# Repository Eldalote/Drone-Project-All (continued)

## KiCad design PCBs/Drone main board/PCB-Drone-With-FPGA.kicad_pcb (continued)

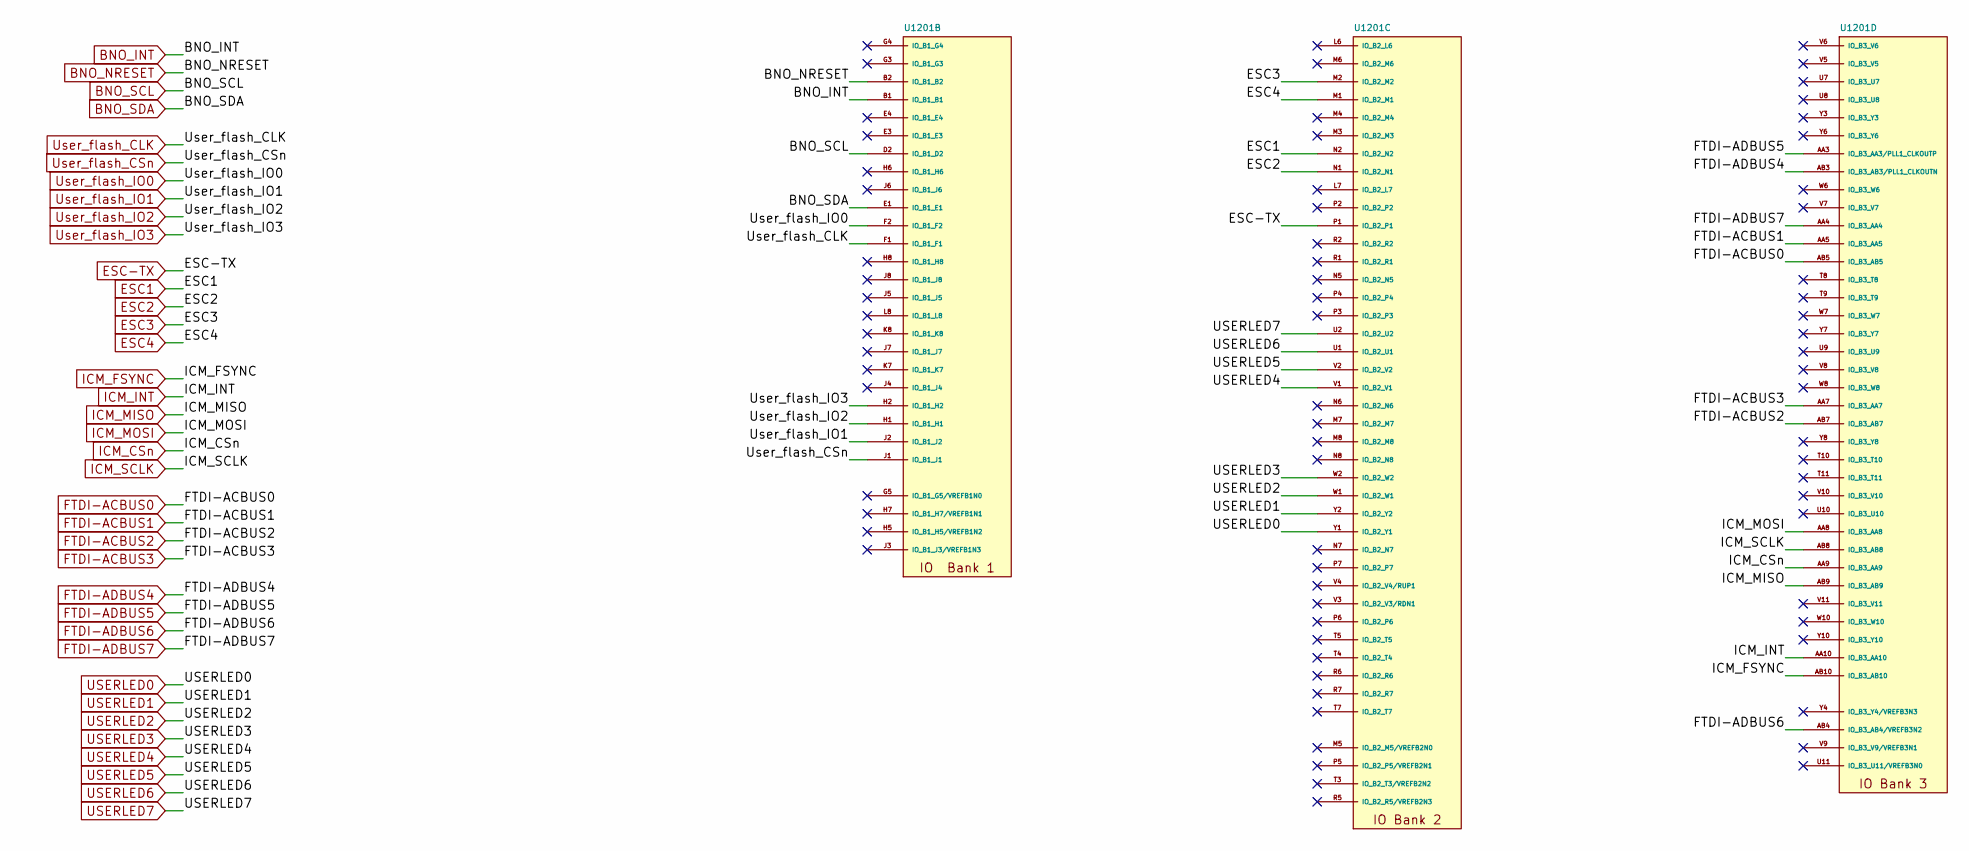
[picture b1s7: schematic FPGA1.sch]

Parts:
U1201: 10CL040_F484; BGA484C100P22X22_2300X2300X200

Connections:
BNO_INT: U1201.B1 (IO_B1_B1); also elsewhere on the board
BNO_NRESET: U1201.B2 (IO_B1_B2); also elsewhere on the board
BNO_SCL: U1201.D2 (IO_B1_D2); also elsewhere on the board
BNO_SDA: U1201.E1 (IO_B1_E1); also elsewhere on the board
ESC1: U1201.N2 (IO_B2_N2); also elsewhere on the board
ESC2: U1201.N1 (IO_B2_N1); also elsewhere on the board
ESC3: U1201.M2 (IO_B2_M2); also elsewhere on the board
ESC4: U1201.M1 (IO_B2_M1); also elsewhere on the board
ESC-TX: U1201.P1 (IO_B2_P1); also elsewhere on the board
FTDI-ACBUS0: U1201.AB5 (IO_B3_AB5); also elsewhere on the board
FTDI-ACBUS1: U1201.AA5 (IO_B3_AA5); also elsewhere on the board
FTDI-ACBUS2: U1201.AB7 (IO_B3_AB7); also elsewhere on the board
FTDI-ACBUS3: U1201.AA7 (IO_B3_AA7); also elsewhere on the board
FTDI-ADBUS4: U1201.AB3 (IO_B3_AB3/PLL1_CLKOUTN); also elsewhere on the board
FTDI-ADBUS5: U1201.AA3 (IO_B3_AA3/PLL1_CLKOUTP); also elsewhere on the board
FTDI-ADBUS6: U1201.AB4 (IO_B3_AB4/VREFB3N2); also elsewhere on the board
FTDI-ADBUS7: U1201.AA4 (IO_B3_AA4); also elsewhere on the board
ICM_CSn: U1201.AA9 (IO_B3_AA9); also elsewhere on the board
ICM_FSYNC: U1201.AB10 (IO_B3_AB10); also elsewhere on the board
ICM_INT: U1201.AA10 (IO_B3_AA10); also elsewhere on the board
ICM_MISO: U1201.AB9 (IO_B3_AB9); also elsewhere on the board
ICM_MOSI: U1201.AA8 (IO_B3_AA8); also elsewhere on the board
ICM_SCLK: U1201.AB8 (IO_B3_AB8); also elsewhere on the board
USERLED0: U1201.Y1 (IO_B2_Y1); also elsewhere on the board
USERLED1: U1201.Y2 (IO_B2_Y2); also elsewhere on the board
USERLED2: U1201.W1 (IO_B2_W1); also elsewhere on the board
USERLED3: U1201.W2 (IO_B2_W2); also elsewhere on the board
USERLED4: U1201.V1 (IO_B2_V1); also elsewhere on the board
USERLED5: U1201.V2 (IO_B2_V2); also elsewhere on the board
USERLED6: U1201.U1 (IO_B2_U1); also elsewhere on the board
USERLED7: U1201.U2 (IO_B2_U2); also elsewhere on the board
User_flash_CLK: U1201.F1 (IO_B1_F1); also elsewhere on the board
User_flash_CSn: U1201.J1 (IO_B1_J1); also elsewhere on the board
User_flash_IO0: U1201.F2 (IO_B1_F2); also elsewhere on the board
User_flash_IO1: U1201.J2 (IO_B1_J2); also elsewhere on the board
User_flash_IO2: U1201.H1 (IO_B1_H1); also elsewhere on the board
User_flash_IO3: U1201.H2 (IO_B1_H2); also elsewhere on the board

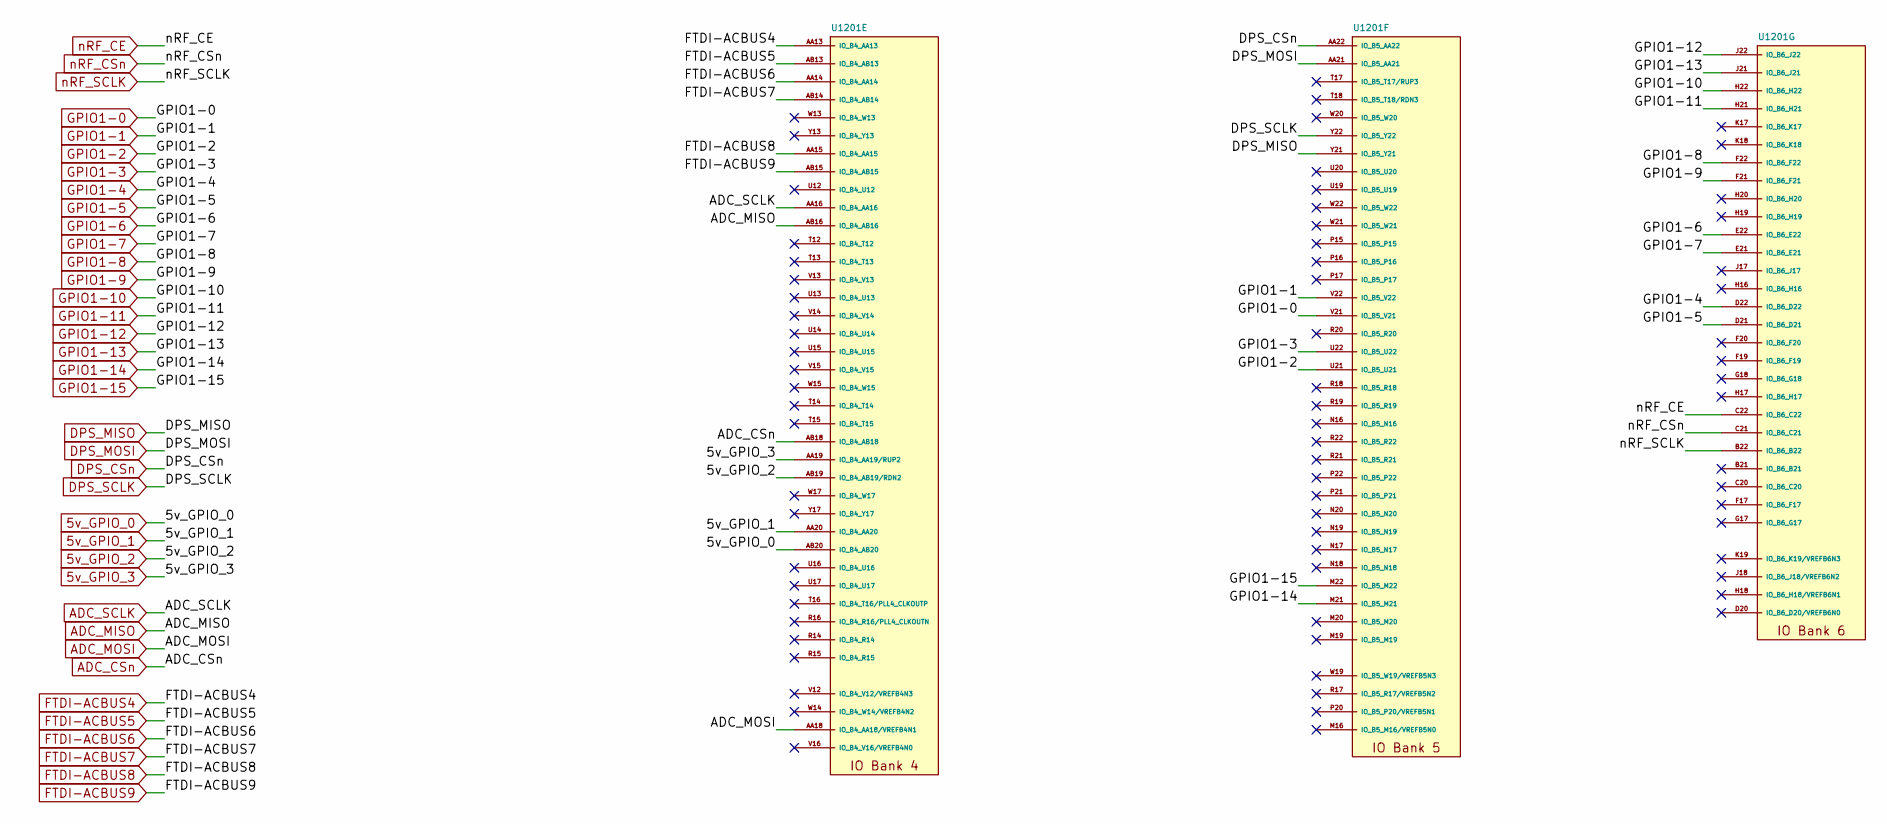
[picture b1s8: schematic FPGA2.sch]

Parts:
U1201: 10CL040_F484; BGA484C100P22X22_2300X2300X200

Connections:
5v_GPIO_0: U1201.AB20 (IO_B4_AB20); also elsewhere on the board
5v_GPIO_1: U1201.AA20 (IO_B4_AA20); also elsewhere on the board
5v_GPIO_2: U1201.AB19 (IO_B4_AB19/RDN2); also elsewhere on the board
5v_GPIO_3: U1201.AA19 (IO_B4_AA19/RUP2); also elsewhere on the board
ADC_CSn: U1201.AB18 (IO_B4_AB18); also elsewhere on the board
ADC_MISO: U1201.AB16 (IO_B4_AB16); also elsewhere on the board
ADC_MOSI: U1201.AA18 (IO_B4_AA18/VREFB4N1); also elsewhere on the board
ADC_SCLK: U1201.AA16 (IO_B4_AA16); also elsewhere on the board
DPS_CSn: U1201.AA22 (IO_B5_AA22); also elsewhere on the board
DPS_MISO: U1201.Y21 (IO_B5_Y21); also elsewhere on the board
DPS_MOSI: U1201.AA21 (IO_B5_AA21); also elsewhere on the board
DPS_SCLK: U1201.Y22 (IO_B5_Y22); also elsewhere on the board
FTDI-ACBUS4: U1201.AA13 (IO_B4_AA13); also elsewhere on the board
FTDI-ACBUS5: U1201.AB13 (IO_B4_AB13); also elsewhere on the board
FTDI-ACBUS6: U1201.AA14 (IO_B4_AA14); also elsewhere on the board
FTDI-ACBUS7: U1201.AB14 (IO_B4_AB14); also elsewhere on the board
FTDI-ACBUS8: U1201.AA15 (IO_B4_AA15); also elsewhere on the board
FTDI-ACBUS9: U1201.AB15 (IO_B4_AB15); also elsewhere on the board
GPIO1-0: U1201.V21 (IO_B5_V21); also elsewhere on the board
GPIO1-1: U1201.V22 (IO_B5_V22); also elsewhere on the board
GPIO1-2: U1201.U21 (IO_B5_U21); also elsewhere on the board
GPIO1-3: U1201.U22 (IO_B5_U22); also elsewhere on the board
GPIO1-4: U1201.D22 (IO_B6_D22); also elsewhere on the board
GPIO1-5: U1201.D21 (IO_B6_D21); also elsewhere on the board
GPIO1-6: U1201.E22 (IO_B6_E22); also elsewhere on the board
GPIO1-7: U1201.E21 (IO_B6_E21); also elsewhere on the board
GPIO1-8: U1201.F22 (IO_B6_F22); also elsewhere on the board
GPIO1-9: U1201.F21 (IO_B6_F21); also elsewhere on the board
GPIO1-10: U1201.H22 (IO_B6_H22); also elsewhere on the board
GPIO1-11: U1201.H21 (IO_B6_H21); also elsewhere on the board
GPIO1-12: U1201.J22 (IO_B6_J22); also elsewhere on the board
GPIO1-13: U1201.J21 (IO_B6_J21); also elsewhere on the board
GPIO1-14: U1201.M21 (IO_B5_M21); also elsewhere on the board
GPIO1-15: U1201.M22 (IO_B5_M22); also elsewhere on the board
nRF_CE: U1201.C22 (IO_B6_C22); also elsewhere on the board
nRF_CSn: U1201.C21 (IO_B6_C21); also elsewhere on the board
nRF_SCLK: U1201.B22 (IO_B6_B22); also elsewhere on the board

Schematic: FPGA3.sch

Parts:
C1401: 100nF; L_0402_1005Metric
R1401, R1402, R1403, R1404: 10k; R_0402_1005Metric
R1405: 10K; R_0402_1005Metric
TP1401, TP1402, TP1403: TestPoint_Small; TestPoint_Pad_D1.0mm
U1201: 10CL040_F484; BGA484C100P22X22_2300X2300X200
X1401: SiT2001BI-S2-33E-50.000000G; SOT-23-5

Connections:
+3V3: C1401.1, R1401.2, R1402.2, R1403.2, R1405.1, X1401.4 (VDD); also elsewhere on the board
/FPGA Part 3/CONF_DONE: R1401.1, TP1401.1, U1201.M18 (CONF_DONE_B6_M18/CONF_DONE)
/FPGA Part 3/CRC_ERROR: TP1403.1, U1201.L21 (IO_B6_L21/CRC_ERROR)
/FPGA Part 3/FPGA-CLOCK-50: U1201.T1 (CLK3_B2_T1/DIFFCLK_1N), X1401.5 (OUT)
/FPGA Part 3/INIT_DONE: TP1402.1, U1201.L22 (IO_B6_L22/INIT_DONE)
/FPGA Part 3/~CE: R1404.2, U1201.L3 (NCE_B1_L3/NCE)
/FPGA Part 3/~CONFIG: R1402.1, U1201.K5 (NCONFIG_B1_K5/NCONFIG)
/FPGA Part 3/~STATUS: R1403.1, U1201.K6 (NSTATUS_B1_K6/NSTATUS)
Conf_flash_CLK: U1201.K2 (IO_B1_K2/DCLK); also elsewhere on the board
Conf_flash_CSn: U1201.E2 (IO_B1_E2/FLASH_NCE,NCSO); also elsewhere on the board
Conf_flash_MISO: U1201.K1 (IO_B1_K1/DATA0); also elsewhere on the board
Conf_flash_MOSI: U1201.D1 (IO_B1_D1/DATA1,ASDO); also elsewhere on the board
GND: C1401.2, R1404.1, U1201.L18 (MSEL1_B6_L18/MSEL1), X1401.1 (GND); also elsewhere on the board
GPIO2-0: U1201.B6 (IO_B8_B6); also elsewhere on the board
GPIO2-1: U1201.A6 (IO_B8_A6); also elsewhere on the board
GPIO2-2: U1201.B7 (IO_B8_B7/DATA4); also elsewhere on the board
GPIO2-3: U1201.A7 (IO_B8_A7); also elsewhere on the board
GPIO2-4: U1201.B18 (IO_B7_B18); also elsewhere on the board
GPIO2-5: U1201.A18 (IO_B7_A18); also elsewhere on the board
GPIO2-6: U1201.B17 (IO_B7_B17); also elsewhere on the board
GPIO2-7: U1201.A17 (IO_B7_A17); also elsewhere on the board
GPIO2-8: U1201.B16 (IO_B7_B16); also elsewhere on the board
GPIO2-9: U1201.A16 (IO_B7_A16); also elsewhere on the board
GPIO2-10: U1201.B15 (IO_B7_B15); also elsewhere on the board
GPIO2-11: U1201.A15 (IO_B7_A15); also elsewhere on the board
GPIO2-12: U1201.B14 (IO_B7_B14); also elsewhere on the board
GPIO2-13: U1201.A14 (IO_B7_A14); also elsewhere on the board
GPIO2-14: U1201.B13 (IO_B7_B13); also elsewhere on the board
GPIO2-15: U1201.A13 (IO_B7_A13); also elsewhere on the board
JTAG_TCK: U1201.L2 (TCK_B1_L2/TCK); also elsewhere on the board
JTAG_TDI: U1201.L5 (TDI_B1_L5/TDI); also elsewhere on the board
JTAG_TDO: U1201.L4 (TDO_B1_L4/TDO); also elsewhere on the board
JTAG_TMS: U1201.L1 (TMS_B1_L1/TMS); also elsewhere on the board
unnamed: R1405.2, X1401.3 (OE)
VCCA: U1201.K20 (MSEL3_B6_K20/MSEL3), U1201.L17 (MSEL2_B6_L17/MSEL2), U1201.M17 (MSEL0_B6_M17/MSEL0); also elsewhere on the board
nRF_IRQ: U1201.B20 (IO_B7_B20/PLL2_CLKOUTP); also elsewhere on the board
nRF_MISO: U1201.A19 (IO_B7_A19/RDN4); also elsewhere on the board
nRF_MOSI: U1201.A20 (IO_B7_A20/PLL2_CLKOUTN); also elsewhere on the board

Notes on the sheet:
Clock Generator

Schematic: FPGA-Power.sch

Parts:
C1501, C1502, C1503, C1504, C1505, C1506, C1507, C1508, C1521, C1528, C1534, C1540: 100nF; L_0402_1005Metric
C1509, C1510, C1511, C1512, C1513, C1514, C1515, C1516, C1519, C1526, C1532, C1538: 4.7uF; C_0402_1005Metric
C1517, C1524, C1531, C1537: 100nF; C_0402_1005Metric
C1518, C1525: 47uF; C_0805_2012Metric
C1520, C1527, C1533, C1539: 1uF; L_0402_1005Metric
C1522, C1529, C1535, C1541: 22nF; L_0402_1005Metric
C1523, C1530, C1536, C1542: 10nF; L_0402_1005Metric
FB1501, FB1502: 180R 1.5A; L_0603_1608Metric
U1201: 10CL040_F484; BGA484C100P22X22_2300X2300X200

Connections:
+1V2: C1518.1, C1519.1, C1520.1, C1521.1, C1522.1, C1523.1, C1525.1, C1526.1, C1527.1, C1528.1, C1529.1, C1530.1, C1532.1, C1533.1, C1534.1, C1535.1, C1536.1, C1538.1, C1539.1, C1540.1, C1541.1, C1542.1, FB1502.1, U1201.G12 (VCCINT_G12), U1201.H9 (VCCINT_H9), U1201.J10 (VCCINT_J10), U1201.J11 (VCCINT_J11), U1201.J12 (VCCINT_J12), U1201.J13 (VCCINT_J13), U1201.J14 (VCCINT_J14), U1201.J16 (VCCINT_J16), U1201.K9 (VCCINT_K9), U1201.K14 (VCCINT_K14), U1201.K15 (VCCINT_K15), U1201.L9 (VCCINT_L9), U1201.L14 (VCCINT_L14), U1201.L16 (VCCINT_L16), U1201.M9 (VCCINT_M9), U1201.M14 (VCCINT_M14), U1201.M15 (VCCINT_M15), U1201.N9 (VCCINT_N9), U1201.N14 (VCCINT_N14), U1201.P9 (VCCINT_P9), U1201.P10 (VCCINT_P10), U1201.P11 (VCCINT_P11), U1201.P12 (VCCINT_P12), U1201.P13 (VCCINT_P13), U1201.P14 (VCCINT_P14), U1201.R8 (VCCINT_R8), U1201.R10 (VCCINT_R10), U1201.R12 (VCCINT_R12); also elsewhere on the board
+2V5: FB1501.1; also elsewhere on the board
+3V3: C1501.1, C1502.1, C1503.1, C1504.1, C1505.1, C1506.1, C1507.1, C1508.1, C1509.1, C1510.1, C1511.1, C1512.1, C1513.1, C1514.1, C1515.1, C1516.1, U1201.A2 (VCCIO8_A2), U1201.A21 (VCCIO7_A21), U1201.AA6 (VCCIO3_AA6), U1201.AB2 (VCCIO3_AB2), U1201.AB21 (VCCIO4_AB21), U1201.D4 (VCCIO1_D4), U1201.D5 (VCCIO8_D5), U1201.D9 (VCCIO8_D9), U1201.D11 (VCCIO8_D11), U1201.D12 (VCCIO7_D12), U1201.D14 (VCCIO7_D14), U1201.D16 (VCCIO7_D16), U1201.D18 (VCCIO7_D18), U1201.E8 (VCCIO8_E8), U1201.E19 (VCCIO6_E19), U1201.F4 (VCCIO1_F4), U1201.G19 (VCCIO6_G19), U1201.H4 (VCCIO1_H4), U1201.J20 (VCCIO6_J20), U1201.K4 (VCCIO1_K4), U1201.L19 (VCCIO6_L19), U1201.N4 (VCCIO2_N4), U1201.P18 (VCCIO5_P18), U1201.R4 (VCCIO2_R4), U1201.T19 (VCCIO5_T19), U1201.U4 (VCCIO2_U4), U1201.V19 (VCCIO5_V19), U1201.W4 (VCCIO2_W4), U1201.W5 (VCCIO3_W5), U1201.W9 (VCCIO3_W9), U1201.W11 (VCCIO3_W11), U1201.W12 (VCCIO4_W12), U1201.W16 (VCCIO4_W16), U1201.W18 (VCCIO4_W18), U1201.Y14 (VCCIO4_Y14), U1201.Y19 (VCCIO5_Y19); also elsewhere on the board
GND: C1501.2, C1502.2, C1503.2, C1504.2, C1505.2, C1506.2, C1507.2, C1508.2, C1509.2, C1510.2, C1511.2, C1512.2, C1513.2, C1514.2, C1515.2, C1516.2, C1517.2, C1518.2, C1519.2, C1520.2, C1521.2, C1522.2, C1523.2, C1524.2, C1525.2, C1526.2, C1527.2, C1528.2, C1529.2, C1530.2, C1531.2, C1532.2, C1533.2, C1534.2, C1535.2, C1536.2, C1537.2, C1538.2, C1539.2, C1540.2, C1541.2, C1542.2, U1201.A1 (GND_A1), U1201.A22 (GND_A22), U1201.AA1 (GND_AA1), U1201.AA2 (GND_AA2), U1201.AA17 (GND_AA17), U1201.AB1 (GND_AB1), U1201.AB6 (GND_AB6), U1201.AB17 (GND_AB17), U1201.AB22 (GND_AB22), U1201.C1 (GND_C1), U1201.C2 (GND_C2), U1201.C5 (GND_C5), U1201.C9 (GND_C9), U1201.C11 (GND_C11), U1201.C12 (GND_C12), U1201.C14 (GND_C14), U1201.C16 (GND_C16), U1201.C18 (GND_C18), U1201.D3 (GND_D3), U1201.D8 (GND_D8), U1201.E18 (GNDA2_E18), U1201.E20 (GND_E20), U1201.F3 (GND_F3), U1201.F5 (GNDA3_F5), U1201.F12 (GND_F12), U1201.G20 (GND_G20), U1201.H3 (GND_H3), U1201.H12 (GND_H12), U1201.H13 (GND_H13), U1201.J9 (GND_J9), U1201.J15 (GND_J15), U1201.J19 (GND_J19), U1201.K3 (GND_K3), U1201.K10 (GND_K10), U1201.K11 (GND_K11), U1201.K12 (GND_K12), U1201.K13 (GND_K13), U1201.K16 (GND_K16), U1201.L10 (GND_L10), U1201.L11 (GND_L11), U1201.L12 (GND_L12), U1201.L13 (GND_L13), U1201.L15 (GND_L15), U1201.L20 (GND_L20), U1201.M10 (GND_M10), U1201.M11 (GND_M11), U1201.M12 (GND_M12), U1201.M13 (GND_M13), U1201.N3 (GND_N3), U1201.N10 (GND_N10), U1201.N11 (GND_N11), U1201.N12 (GND_N12), U1201.N13 (GND_N13), U1201.N15 (GND_N15), U1201.P8 (GND_P8), U1201.P19 (GND_P19), U1201.R3 (GND_R3), U1201.R9 (GND_R9), U1201.R11 (GND_R11), U1201.R13 (GND_R13), U1201.T20 (GND_T20), U1201.U3 (GND_U3), U1201.U5 (GNDA1_U5), U1201.V18 (GNDA4_V18), U1201.V20 (GND_V20), U1201.W3 (GND_W3), U1201.Y5 (GND_Y5), U1201.Y9 (GND_Y9), U1201.Y11 (GND_Y11), U1201.Y12 (GND_Y12), U1201.Y15 (GND_Y15), U1201.Y16 (GND_Y16), U1201.Y18 (GND_Y18), U1201.Y20 (GND_Y20); also elsewhere on the board
VCCA: C1517.1, C1524.1, FB1501.2, U1201.F18 (VCCA2_F18), U1201.G6 (VCCA3_G6), U1201.T6 (VCCA1_T6), U1201.U18 (VCCA4_U18); also elsewhere on the board
VCCD_PLL: C1531.1, C1537.1, FB1502.2, U1201.E17 (VCCD_PLL2_E17), U1201.F6 (VCCD_PLL3_F6), U1201.U6 (VCCD_PLL1_U6), U1201.V17 (VCCD_PLL4_V17)

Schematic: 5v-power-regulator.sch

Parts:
C301: 10uF 25v; C_0805_2012Metric
C302: 100nF 25v; C_0805_2012Metric
C303, C304: 22uF 25v; C_0805_2012Metric
L301: 4.7uH 2.6ADC; L_5030_TAIYO_YUDEN
U301: AP63205WU-7; SOT95P280X100-6N

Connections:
+10V: C301.1, U301.2 (EN), U301.3 (VIN); also elsewhere on the board
/Power Distribution and Estimation/5v Power regulator/5v_BST: C302.1, U301.6 (BST)
/Power Distribution and Estimation/5v Power regulator/5v_SW: C302.2, L301.1, U301.5 (SW)
/Power Distribution and Estimation/5v-regulator: C303.1, C304.1, L301.2, U301.1 (FB); also elsewhere on the board
GND: C301.2, C303.2, C304.2, U301.4 (GND); also elsewhere on the board

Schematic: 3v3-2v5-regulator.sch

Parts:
C401: 10uF; C_0805_2012Metric
C402, C403: 1uF; C_0603_1608Metric
C404: 22uF; C_0805_2012Metric
L401: 1uH; L_3012_TDK
U401: SC189ZSKTRT; SOT95P280X145-5N
U402: NCP115ASN250T2G; SOT95P275X110-5N

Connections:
+2V5: C403.1, U402.5 (OUT); also elsewhere on the board
+3V3: C402.1, C404.1, L401.2, U401.4 (VOUT), U402.1 (IN), U402.3 (EN); also elsewhere on the board
+5V: C401.1, U401.1 (VIN), U401.3 (EN); also elsewhere on the board
/Power Distribution and Estimation/3v3 and 2v5 power regulators/3v3_LX: L401.1, U401.5 (LX)
GND: C401.2, C402.2, C403.2, C404.2, U401.2 (GND), U402.2 (GND), U402.4 (N/C); also elsewhere on the board

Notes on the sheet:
3v3 Regulator (top)
2v5 LDO (top)

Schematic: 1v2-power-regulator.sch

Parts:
C501: 10uF; C_0805_2012Metric
C502: 100nF; C_0402_1005Metric
C503: 100pF; C_0402_1005Metric
C504, C505: 22uF; C_0805_2012Metric
L501: 2.2uH; L_4018_Bourns
R501: 30k9; R_0402_1005Metric
R502: 62k; R_0402_1005Metric
U501: AP63200WU-7; SOT95P280X100-6N

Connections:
+1V2: C503.1, C504.1, C505.1, L501.2, R501.1; also elsewhere on the board
+5V: C501.1, U501.2 (EN), U501.3 (VIN); also elsewhere on the board
/Power Distribution and Estimation/1v2 power regulator/1v2_BST: C502.1, U501.6 (BST)
/Power Distribution and Estimation/1v2 power regulator/1v2_FB: C503.2, R501.2, R502.1, U501.1 (FB)
/Power Distribution and Estimation/1v2 power regulator/1v2_SW: C502.2, L501.1, U501.5 (SW)
GND: C501.2, C504.2, C505.2, R502.2, U501.4 (GND); also elsewhere on the board

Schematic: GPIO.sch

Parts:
J1001, J1003: Conn_02x10; PinHeader_2x10_P2.54mm_Vertical
J1002: Conn_02x07; PinHeader_2x07_P2.54mm_Vertical
J1004: Conn_02x05; PinHeader_2x05_P2.54mm_Vertical
R1001, R1002: 10k; R_0402_1005Metric
R1003: 1k; R_0402_1005Metric

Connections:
5v_GPIO_5v_0: J1002.3; also elsewhere on the board
5v_GPIO_5v_1: J1002.4; also elsewhere on the board
5v_GPIO_5v_2: J1002.5; also elsewhere on the board
5v_GPIO_5v_3: J1002.6; also elsewhere on the board
+3V3: J1001.1, J1001.2, J1003.1, J1003.2; also elsewhere on the board
+5V: J1002.1, J1002.2; also elsewhere on the board
ADC_CH2: J1002.12; also elsewhere on the board
ADC_CH3: J1002.11; also elsewhere on the board
ADC_CH4: J1002.10; also elsewhere on the board
ADC_CH5: J1002.9; also elsewhere on the board
ADC_CH6: J1002.8; also elsewhere on the board
ADC_CH7: J1002.7; also elsewhere on the board
GND: J1001.19, J1001.20, J1002.14, J1003.19, J1003.20, J1004.2, J1004.10, R1003.2; also elsewhere on the board
GNDA: J1002.13; also elsewhere on the board
GPIO1-0: J1001.3; also elsewhere on the board
GPIO1-1: J1001.4; also elsewhere on the board
GPIO1-2: J1001.5; also elsewhere on the board
GPIO1-3: J1001.6; also elsewhere on the board
GPIO1-4: J1001.7; also elsewhere on the board
GPIO1-5: J1001.8; also elsewhere on the board
GPIO1-6: J1001.9; also elsewhere on the board
GPIO1-7: J1001.10; also elsewhere on the board
GPIO1-8: J1001.11; also elsewhere on the board
GPIO1-9: J1001.12; also elsewhere on the board
GPIO1-10: J1001.13; also elsewhere on the board
GPIO1-11: J1001.14; also elsewhere on the board
GPIO1-12: J1001.15; also elsewhere on the board
GPIO1-13: J1001.16; also elsewhere on the board
GPIO1-14: J1001.17; also elsewhere on the board
GPIO1-15: J1001.18; also elsewhere on the board
GPIO2-0: J1003.3; also elsewhere on the board
GPIO2-1: J1003.4; also elsewhere on the board
GPIO2-2: J1003.5; also elsewhere on the board
GPIO2-3: J1003.6; also elsewhere on the board
GPIO2-4: J1003.7; also elsewhere on the board
GPIO2-5: J1003.8; also elsewhere on the board
GPIO2-6: J1003.9; also elsewhere on the board
GPIO2-7: J1003.10; also elsewhere on the board
GPIO2-8: J1003.11; also elsewhere on the board
GPIO2-9: J1003.12; also elsewhere on the board
GPIO2-10: J1003.13; also elsewhere on the board
GPIO2-11: J1003.14; also elsewhere on the board
GPIO2-12: J1003.15; also elsewhere on the board
GPIO2-13: J1003.16; also elsewhere on the board
GPIO2-14: J1003.17; also elsewhere on the board
GPIO2-15: J1003.18; also elsewhere on the board
JTAG_TCK: J1004.1, R1003.1; also elsewhere on the board
JTAG_TDI: J1004.9, R1001.2; also elsewhere on the board
JTAG_TDO: J1004.3; also elsewhere on the board
JTAG_TMS: J1004.5, R1002.2; also elsewhere on the board
VCCA: J1004.4, R1001.1, R1002.1; also elsewhere on the board

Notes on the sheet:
JTAG (top)
Sheet IO
5 Volt GPIO and ADC connector
3.3 Volt GPIO Connectors

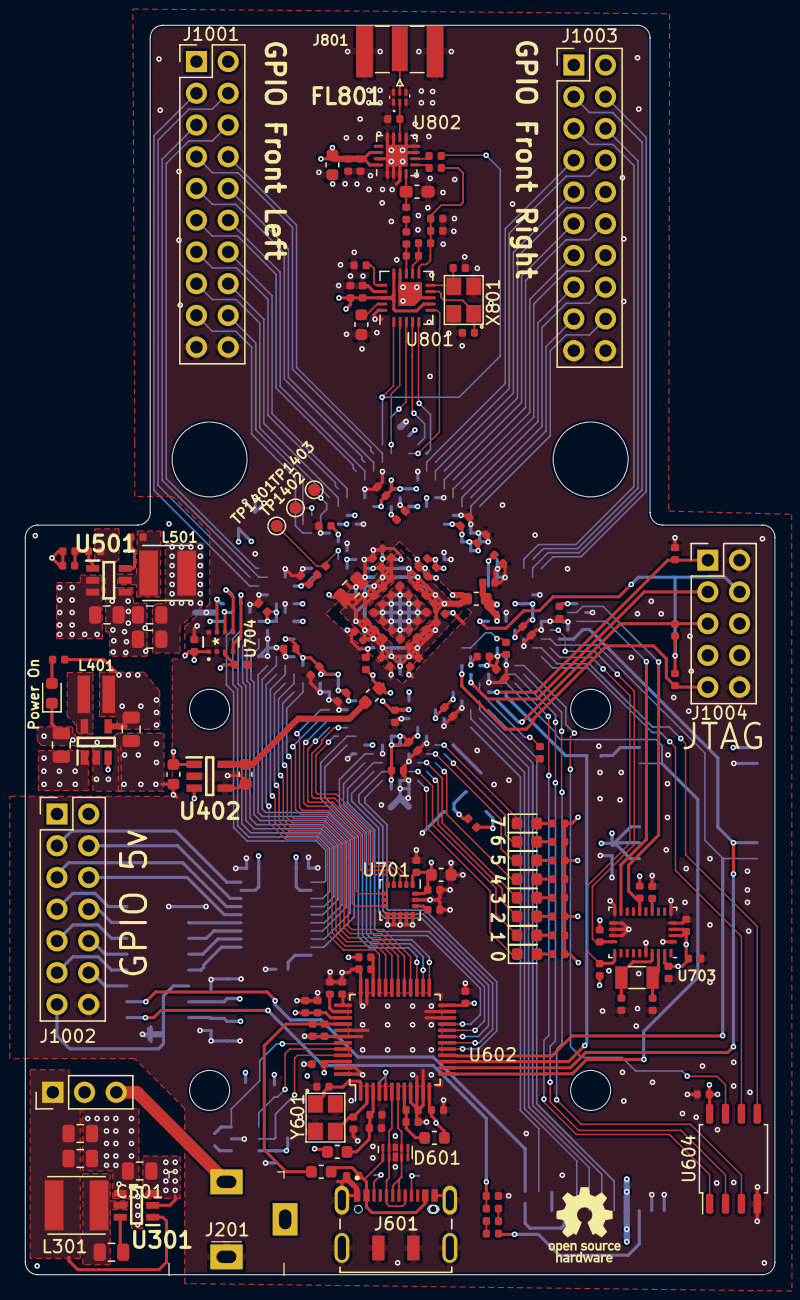
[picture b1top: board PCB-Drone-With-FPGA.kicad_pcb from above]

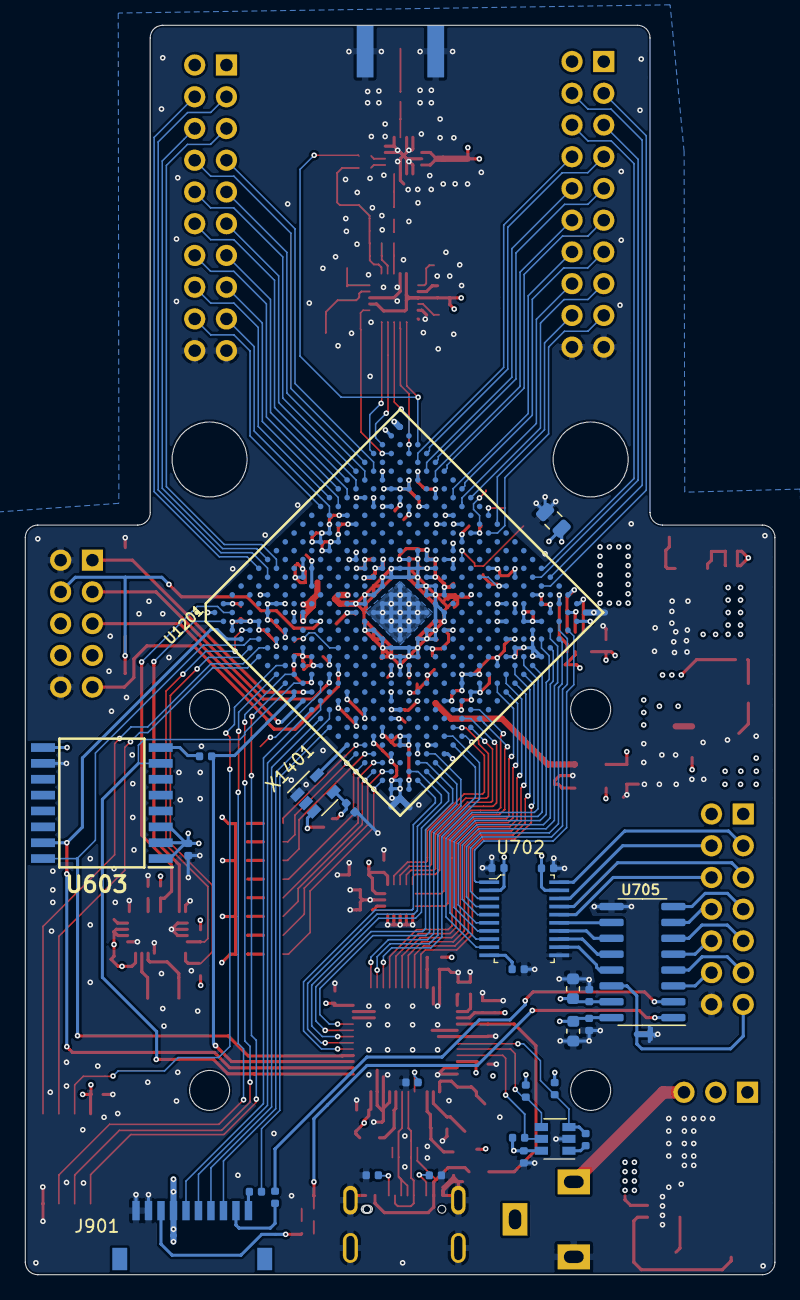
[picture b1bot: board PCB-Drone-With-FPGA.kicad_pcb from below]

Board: 4 copper layers, 60.0 x 100.0 mm, 210 parts (29 on the bottom side), 195 nets.

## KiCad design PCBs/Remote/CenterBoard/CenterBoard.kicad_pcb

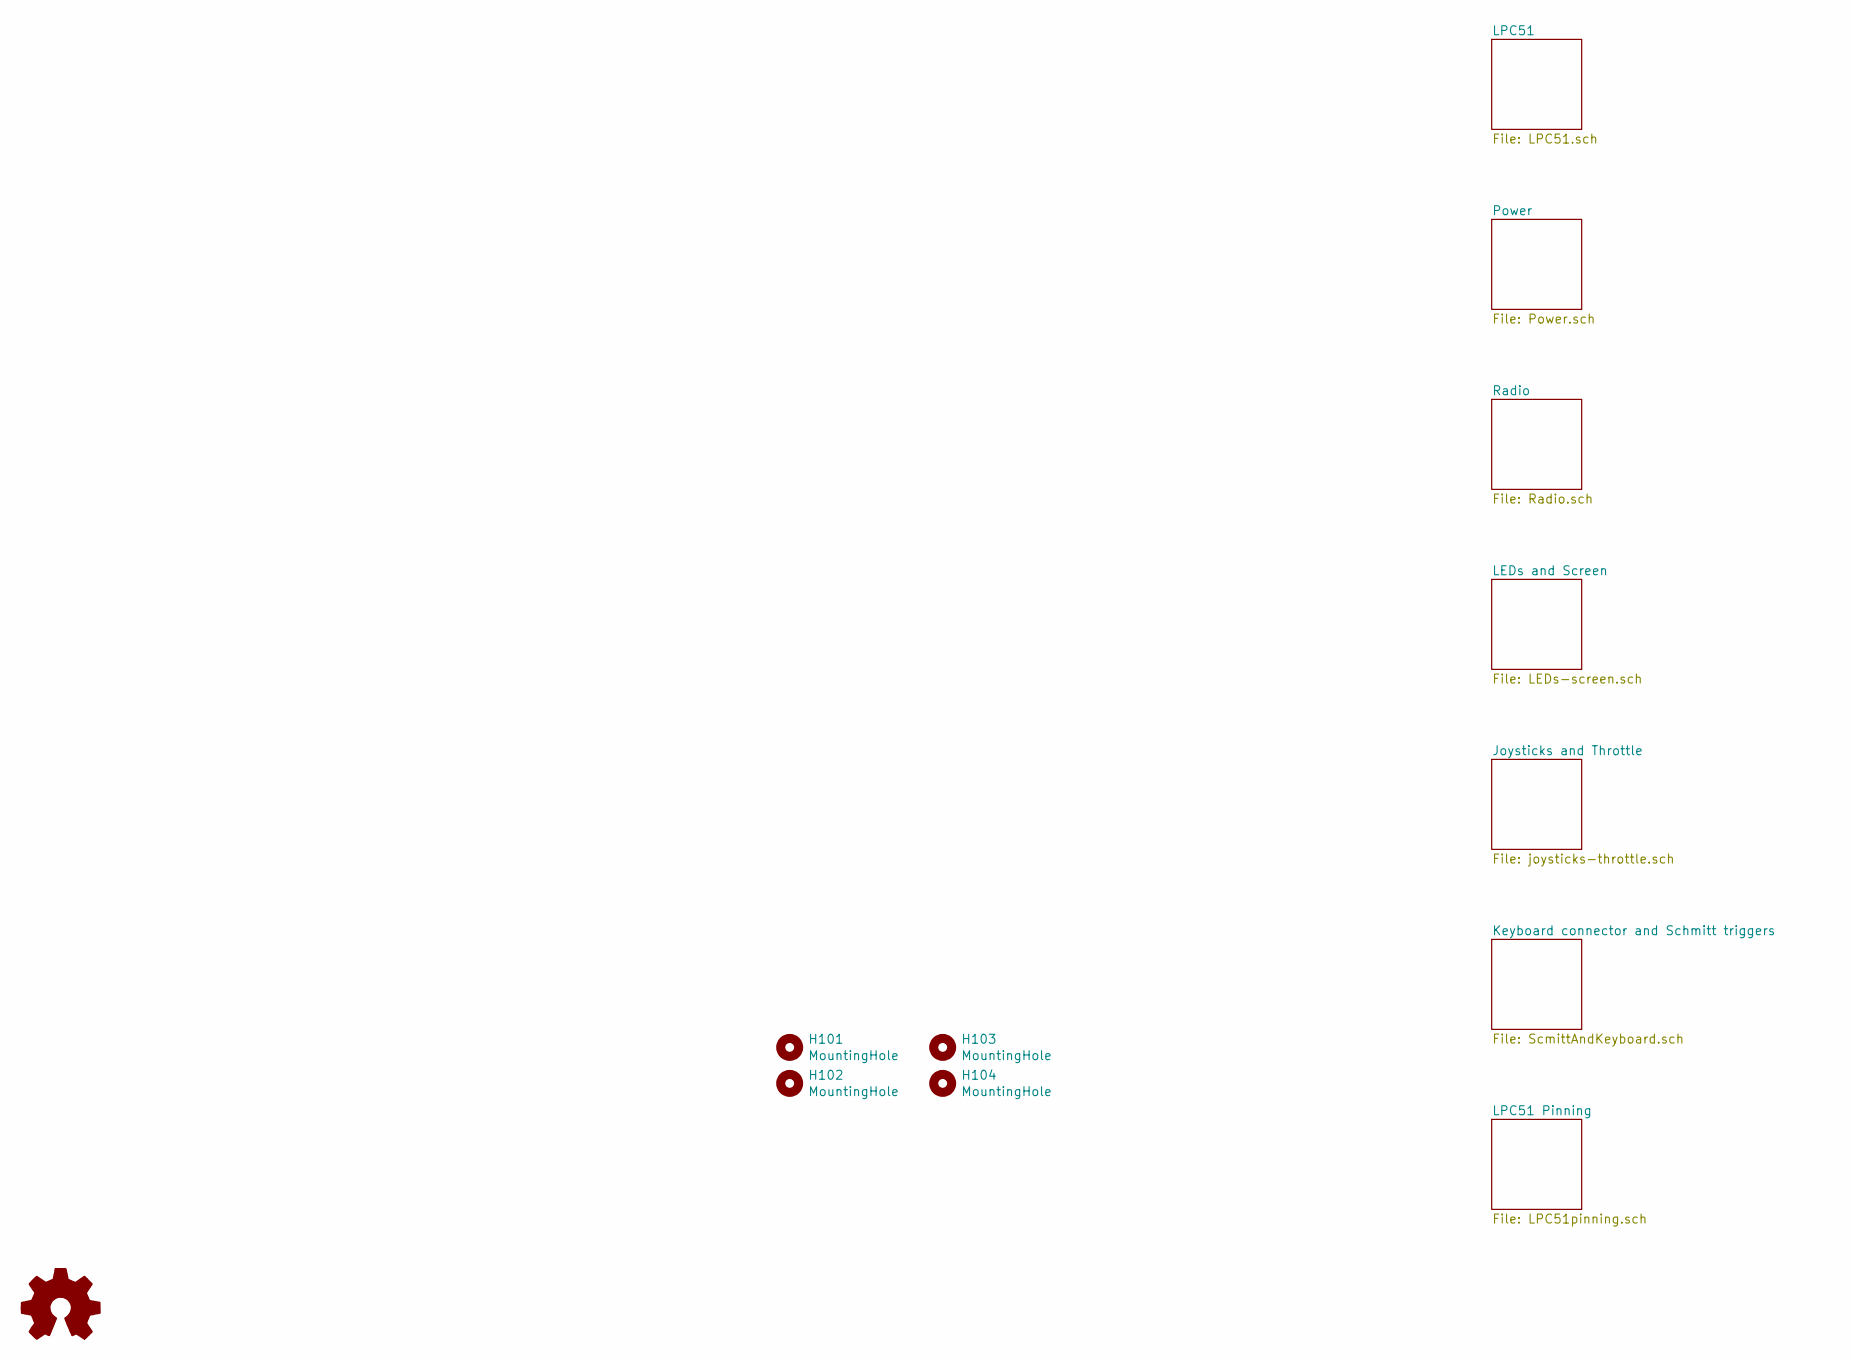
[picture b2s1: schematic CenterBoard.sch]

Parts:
H101, H102, H103, H104: MountingHole; MountingHole_3.2mm_M3_ISO7380
LOGO101: Logo_Open_Hardware_Small; OSHW-Logo_5.7x6mm_SilkScreen
